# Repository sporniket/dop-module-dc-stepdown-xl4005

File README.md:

# DOP (Delivery Of Power) Module

> [WARNING] Please read carefully this note before using this project. It contains important facts.

Content

1. What is **DOP (Delivery Of Power) Module**, and when to use it ?
2. What should you know before using **DOP (Delivery Of Power) Module** ?
3. How to use **DOP (Delivery Of Power) Module** ?
4. Known issues
5. Miscellanous

## 1. What is **DOP (Delivery Of Power) Module**, and when to use it ?

**DOP (Delivery Of Power) Module** is a dc-dc stepdown module based on the XL4005 by XLSEMI.

### Licence

**DOP (Delivery Of Power) Module** is published under the Creative Commons CC0 license. You can find a copy of the licence there : https://creativecommons.org/publicdomain/zero/1.0/legalcode

You can copy, modify, distribute and perform the work, even for commercial purposes, all without asking permission.

**DOP (Delivery Of Power) Module** is distributed in the hope that it will be useful, but WITHOUT ANY WARRANTY; without even the implied warranty of MERCHANTABILITY or FITNESS FOR A PARTICULAR PURPOSE.

### Release notes

#### v1.0.0

* Schematic, gerbers, bom and cpl files to get CMS assembled.

The 2K variable resistor seems discontinued. At least, it was unavailable at LCSC at time of ordering the first batch.

A selection for the big capacitors, the inductor, and the trimming potentiometer :

|Manufacturer|Mfr. No|Description |
|---|---|---|
|Rubycon|50ZLJ470M12.5X16|Aluminium Electrolytic Capacitors - Radial Leaded LOW IMPEDANCE ELECTROLYTIC CAPACITORS|
|Rubycon|50YXJ470M12.5X20|Aluminium Electrolytic Capacitors - Radial Leaded LOW IMPEDANCE ELECTROLYTIC CAPACITORS|
|KEMET|A759PY687M1HAAE026|Aluminium Organic Polymer Capacitors 50Vol 680uF RAD 2KHr ESR=26 mOhms|
|Coilcraft|VER2923-333KL|Power Inductors - Leaded 33uH Shld 10% 26A 2.6mOhms|
|Coilcraft|AGP2923-333KL|Power Inductors - Leaded 33uH Shld 10% 26A 2.6mOhms AECQ2|
|Bourns|3214W-2-202E|Trimmer Resistors - SMD 4MM SQ MT CERMET TRIMMER SMD|
|Bourns|3214W-1-202G|Trimmer Resistors - SMD 4MM SQ 2KOHMS 10% 5TURN|
|Bourns|3214W-1-202E|Trimmer Resistors - SMD 4mm SQ 2K OHM|

## 2. What should you know before using **DOP (Delivery Of Power) Module** ?

**DOP (Delivery Of Power) Module** is made using Kicad 5.

> Do not use **DOP (Delivery Of Power) Module** if this project is not suitable for your project.

## 3. How to use **DOP (Delivery Of Power) Module** ?

### From sources

To get the latest available work, one must clone the git repository, build and install the package.

	git clone https://github.com/sporniket/dop-module-dc-stepdown-xl4005.git

Then, open the project with Kicad 5.

## 4. Known issues
See the [project issues](https://github.com/sporniket/dop-module-dc-stepdown-xl4005/issues) page.

## 5. Miscellanous

### Report issues
Use the [project issues](https://github.com/sporniket/dop-module-dc-stepdown-xl4005/issues) page.

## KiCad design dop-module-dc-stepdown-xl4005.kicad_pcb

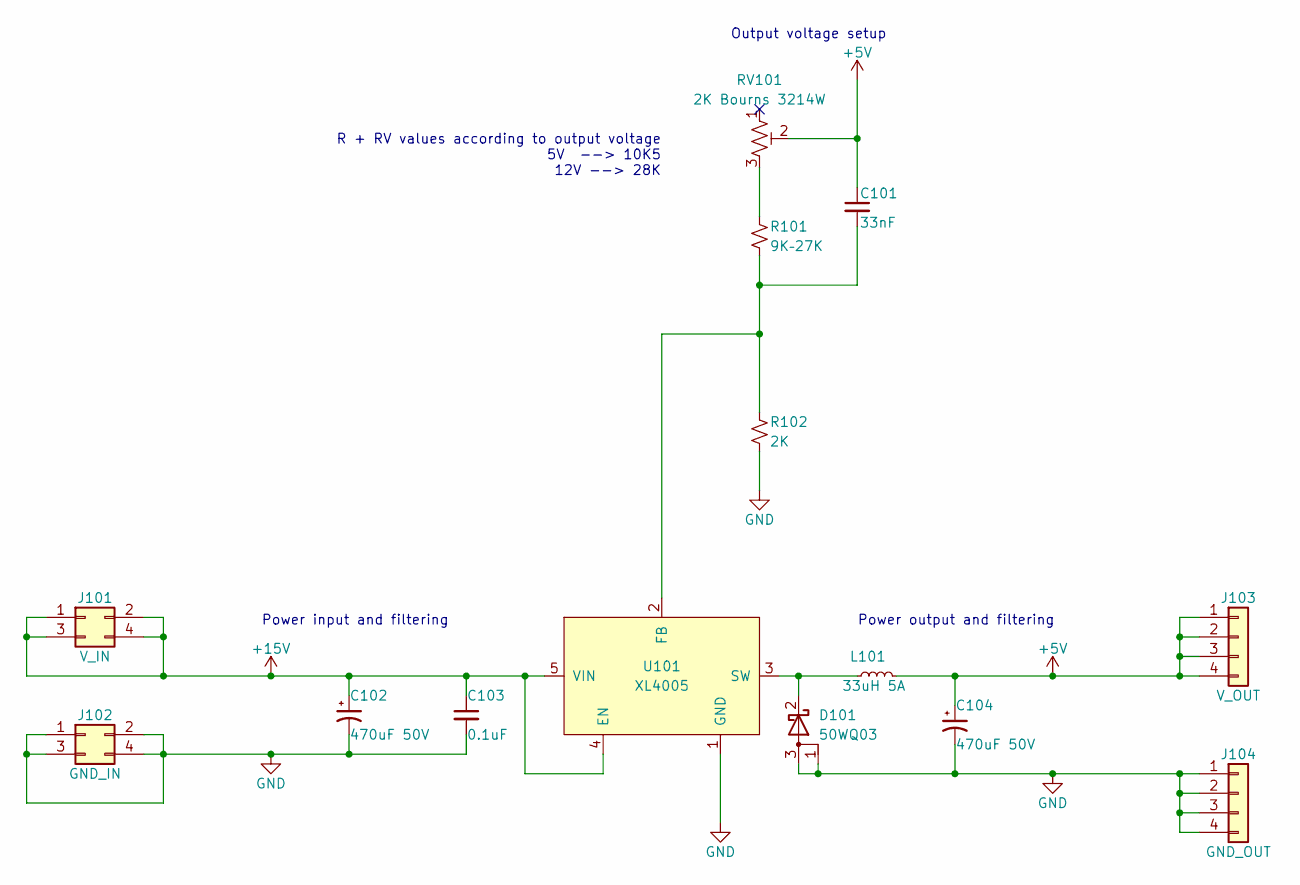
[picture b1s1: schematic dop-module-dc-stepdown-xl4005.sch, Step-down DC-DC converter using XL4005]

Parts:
C101: 33nF; C_1206_3216Metric_Pad1.33x1.80mm_HandSolder; LCSC C318778
C102, C104: 470uF 50V; CP_Radial_D13.0mm_P5.00mm
C103: 0.1uF; C_1206_3216Metric_Pad1.33x1.80mm_HandSolder; LCSC C24497
D101: 50WQ03; TO-252-2; LCSC C222476
J101: V_IN; PinHeader_2x02_P2.54mm_Vertical
J102: GND_IN; PinHeader_2x02_P2.54mm_Vertical
J103: V_OUT; PinHeader_1x04_P2.54mm_Vertical
J104: GND_OUT; PinHeader_1x04_P2.54mm_Vertical
L101: 33uH 5A; CoilCraft_AGP2923
R101: 9K–27K; R_1206_3216Metric_Pad1.30x1.75mm_HandSolder; LCSC C2984531
R102: 2K; R_1206_3216Metric_Pad1.30x1.75mm_HandSolder; LCSC C844028
RV101: 2K Bourns 3214W; Potentiometer_Bourns_3214W_Vertical; LCSC C780202
U101: XL4005; TO-263-5_TabPin3; LCSC C73332

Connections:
+5V: C101.1, C104.1, J103.1, J103.2, J103.3, J103.4, L101.2, RV101.2
+15V: C102.1, C103.1, J101.1, J101.2, J101.3, J101.4, U101.4 (EN), U101.5 (VIN)
GND: C102.2, C103.2, C104.2, D101.1 (A), D101.3 (A), J102.1, J102.2, J102.3, J102.4, J104.1, J104.2, J104.3, J104.4, R102.2, U101.1 (GND)
unnamed: C101.2, R101.2, R102.1, U101.2 (FB)
unnamed: D101.2 (K), L101.1, U101.3 (SW)
unnamed: R101.1, RV101.3

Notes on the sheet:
Output voltage setup
R + RV values according to output voltage 5V --> 10K5 12V --> 28K
Power output and filtering
Power input and filtering

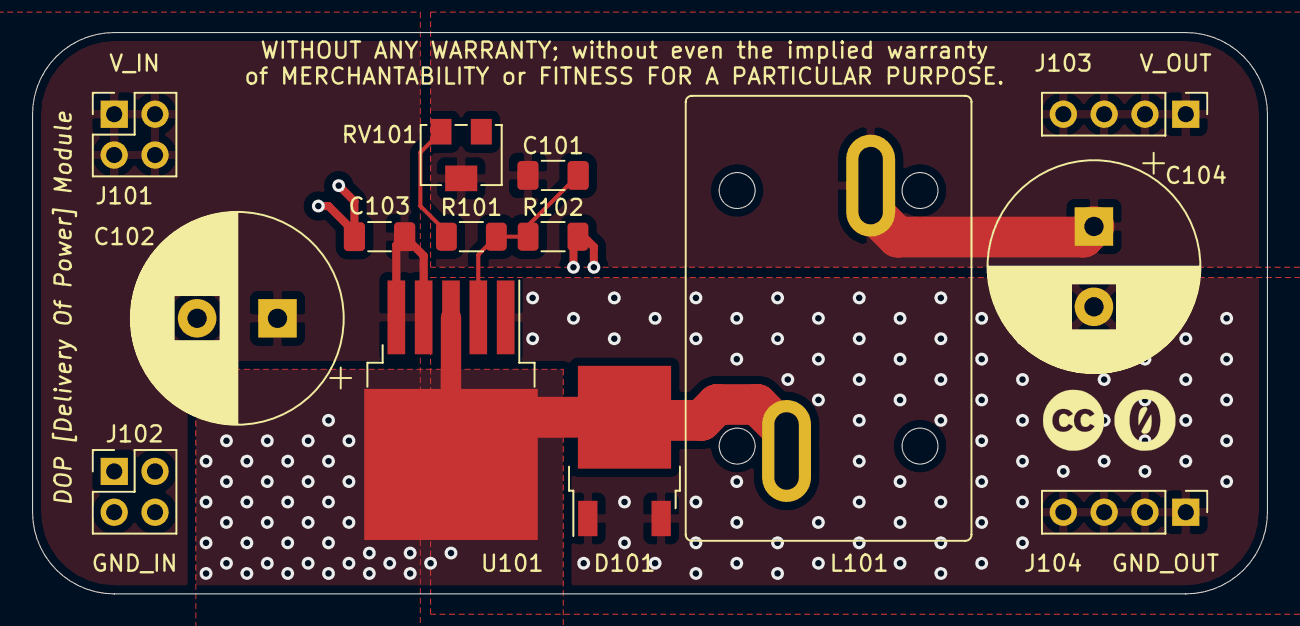
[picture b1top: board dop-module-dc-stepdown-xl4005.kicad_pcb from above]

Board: 2 copper layers, 76.8 x 34.9 mm, 14 parts (0 on the bottom side), 6 nets.

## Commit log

2022-01-21 first draft
2022-01-22 compact layout in progress
2022-01-23 done : components, traces, pours, edge
2022-01-23 done : silk screen front and back
2022-01-23 done : no more castellation, final
2022-01-24 done : adjust back silkscreen
2022-01-24 inductor datasheet
2022-01-26 update 3dshapes
2022-01-26 update 3d model for the trimpot
2022-02-03 update 3dshapes submodule
2022-02-03 use 3d model for inductor
2022-02-06 add 3d shape of connector
2022-02-06 add preview gallery
2022-06-02 replace J101 and J102 by explicit 2x08 pin headers
2022-06-02 full redesign of the pcb
2022-11-20 complete rework
2022-11-21 add copper pour for heat dissipation on the bottom, fixes DRC violations
2022-11-23 update cartridge, center pcb in worksheet, use new page description
2022-11-23 add CC0 license text
2022-11-23 prepare README
2022-11-25 add LCSC skus for generating bom
2022-11-25 update gallery
2022-11-25 setup export gerber
2022-12-02 prepare release : version
2022-12-02 make origin at 0,0 to export correct centroid file
2022-12-02 prepare release : version of PCB
2022-12-02 remove unnecessary library
2022-12-02 prepare release : readme -- bom for missing components except connectors
